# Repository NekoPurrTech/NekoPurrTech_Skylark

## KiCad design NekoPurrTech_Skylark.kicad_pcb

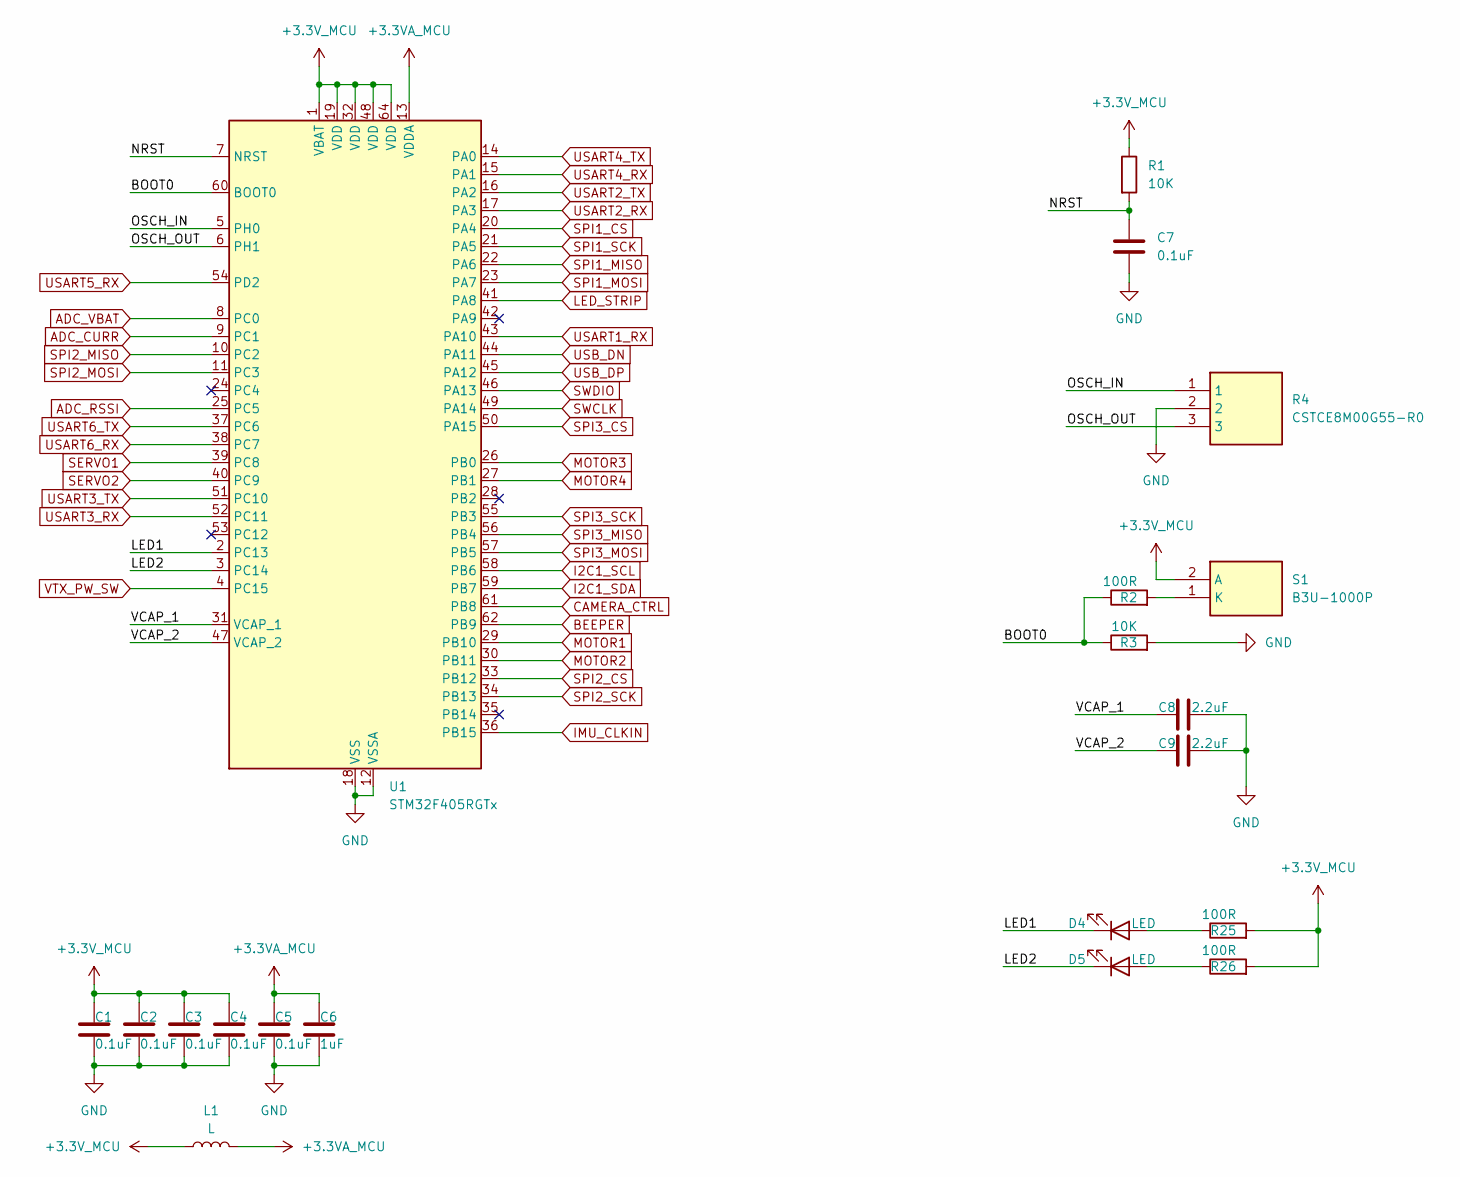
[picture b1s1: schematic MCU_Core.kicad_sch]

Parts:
C1, C2, C3, C4, C5, C7: 0.1uF; C_0402_1005Metric
C6: 1uF; C_0402_1005Metric
C8, C9: 2.2uF; C_0402_1005Metric
D4, D5: LED; LED_0603_1608Metric
L1: L; L_0603_1608Metric
R1, R3: 10K; R_0402_1005Metric
R2, R25, R26: 100R; R_0402_1005Metric
R4: CSTCE8M00G55-R0; CSTCE12M0G55-R0; Manufacturer_Part_Number CSTCE8M00G55-R0; Mouser Part Number 81-CSTCE8M00G55-R0
S1: B3U-1000P; Manufacturer_Part_Number B3U-1000P; Mouser Part Number 653-B3U-1000P
U1: STM32F405RGTx; LQFP-64_10x10mm_P0.5mm

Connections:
+3.3VA_MCU: C5.1, C6.1, L1.2, U1.13 (VDDA)
+3.3V_MCU: C1.1, C2.1, C3.1, C4.1, L1.1, R1.1, R25.2, R26.2, S1.2 (A), U1.1 (VBAT), U1.19 (VDD), U1.32 (VDD), U1.48 (VDD), U1.64 (VDD); also elsewhere on the board
/MCU_Core/BOOT0: R2.1, R3.1, U1.60 (BOOT0)
/MCU_Core/LED1: D4.1 (K), U1.2 (PC13)
/MCU_Core/LED2: D5.1 (K), U1.3 (PC14)
/MCU_Core/NRST: C7.1, R1.2, U1.7 (NRST)
/MCU_Core/OSCH_IN: R4.1, U1.5 (PH0)
/MCU_Core/OSCH_OUT: R4.3, U1.6 (PH1)
/MCU_Core/VCAP_1: C8.1, U1.31 (VCAP_1)
/MCU_Core/VCAP_2: C9.1, U1.47 (VCAP_2)
ADC_CURR: U1.9 (PC1); also elsewhere on the board
ADC_RSSI: U1.25 (PC5); also elsewhere on the board
ADC_VBAT: U1.8 (PC0); also elsewhere on the board
BEEPER: U1.62 (PB9); also elsewhere on the board
CAMERA_CTRL: U1.61 (PB8); also elsewhere on the board
GND: C1.2, C2.2, C3.2, C4.2, C5.2, C6.2, C7.2, C8.2, C9.2, R3.2, R4.2, U1.12 (VSSA), U1.18 (VSS), U1.63 (VSS); also elsewhere on the board
I2C1_SCL: U1.58 (PB6); also elsewhere on the board
I2C1_SDA: U1.59 (PB7); also elsewhere on the board
IMU_CLKIN: U1.36 (PB15); also elsewhere on the board
LED_STRIP: U1.41 (PA8); also elsewhere on the board
MOTOR1: U1.29 (PB10); also elsewhere on the board
MOTOR2: U1.30 (PB11); also elsewhere on the board
MOTOR3: U1.26 (PB0); also elsewhere on the board
MOTOR4: U1.27 (PB1); also elsewhere on the board
unnamed: D4.2 (A), R25.1
unnamed: D5.2 (A), R26.1
unnamed: R2.2, S1.1 (K)
SERVO1: U1.39 (PC8); also elsewhere on the board
SERVO2: U1.40 (PC9); also elsewhere on the board
SPI1_CS: U1.20 (PA4); also elsewhere on the board
SPI1_MISO: U1.22 (PA6); also elsewhere on the board
SPI1_MOSI: U1.23 (PA7); also elsewhere on the board
SPI1_SCK: U1.21 (PA5); also elsewhere on the board
SPI2_CS: U1.33 (PB12); also elsewhere on the board
SPI2_MISO: U1.10 (PC2); also elsewhere on the board
SPI2_MOSI: U1.11 (PC3); also elsewhere on the board
SPI2_SCK: U1.34 (PB13); also elsewhere on the board
SPI3_CS: U1.50 (PA15); also elsewhere on the board
SPI3_MISO: U1.56 (PB4); also elsewhere on the board
SPI3_MOSI: U1.57 (PB5); also elsewhere on the board
SPI3_SCK: U1.55 (PB3); also elsewhere on the board
SWCLK: U1.49 (PA14)
SWDIO: U1.46 (PA13)
USART1_RX: U1.43 (PA10); also elsewhere on the board
USART2_RX: U1.17 (PA3); also elsewhere on the board
USART2_TX: U1.16 (PA2); also elsewhere on the board
USART3_RX: U1.52 (PC11); also elsewhere on the board
USART3_TX: U1.51 (PC10); also elsewhere on the board
USART4_RX: U1.15 (PA1); also elsewhere on the board
USART4_TX: U1.14 (PA0); also elsewhere on the board
USART5_RX: U1.54 (PD2); also elsewhere on the board
USART6_RX: U1.38 (PC7); also elsewhere on the board
USART6_TX: U1.37 (PC6); also elsewhere on the board
USB_DN: U1.44 (PA11); also elsewhere on the board
USB_DP: U1.45 (PA12); also elsewhere on the board
VTX_PW_SW: U1.4 (PC15)

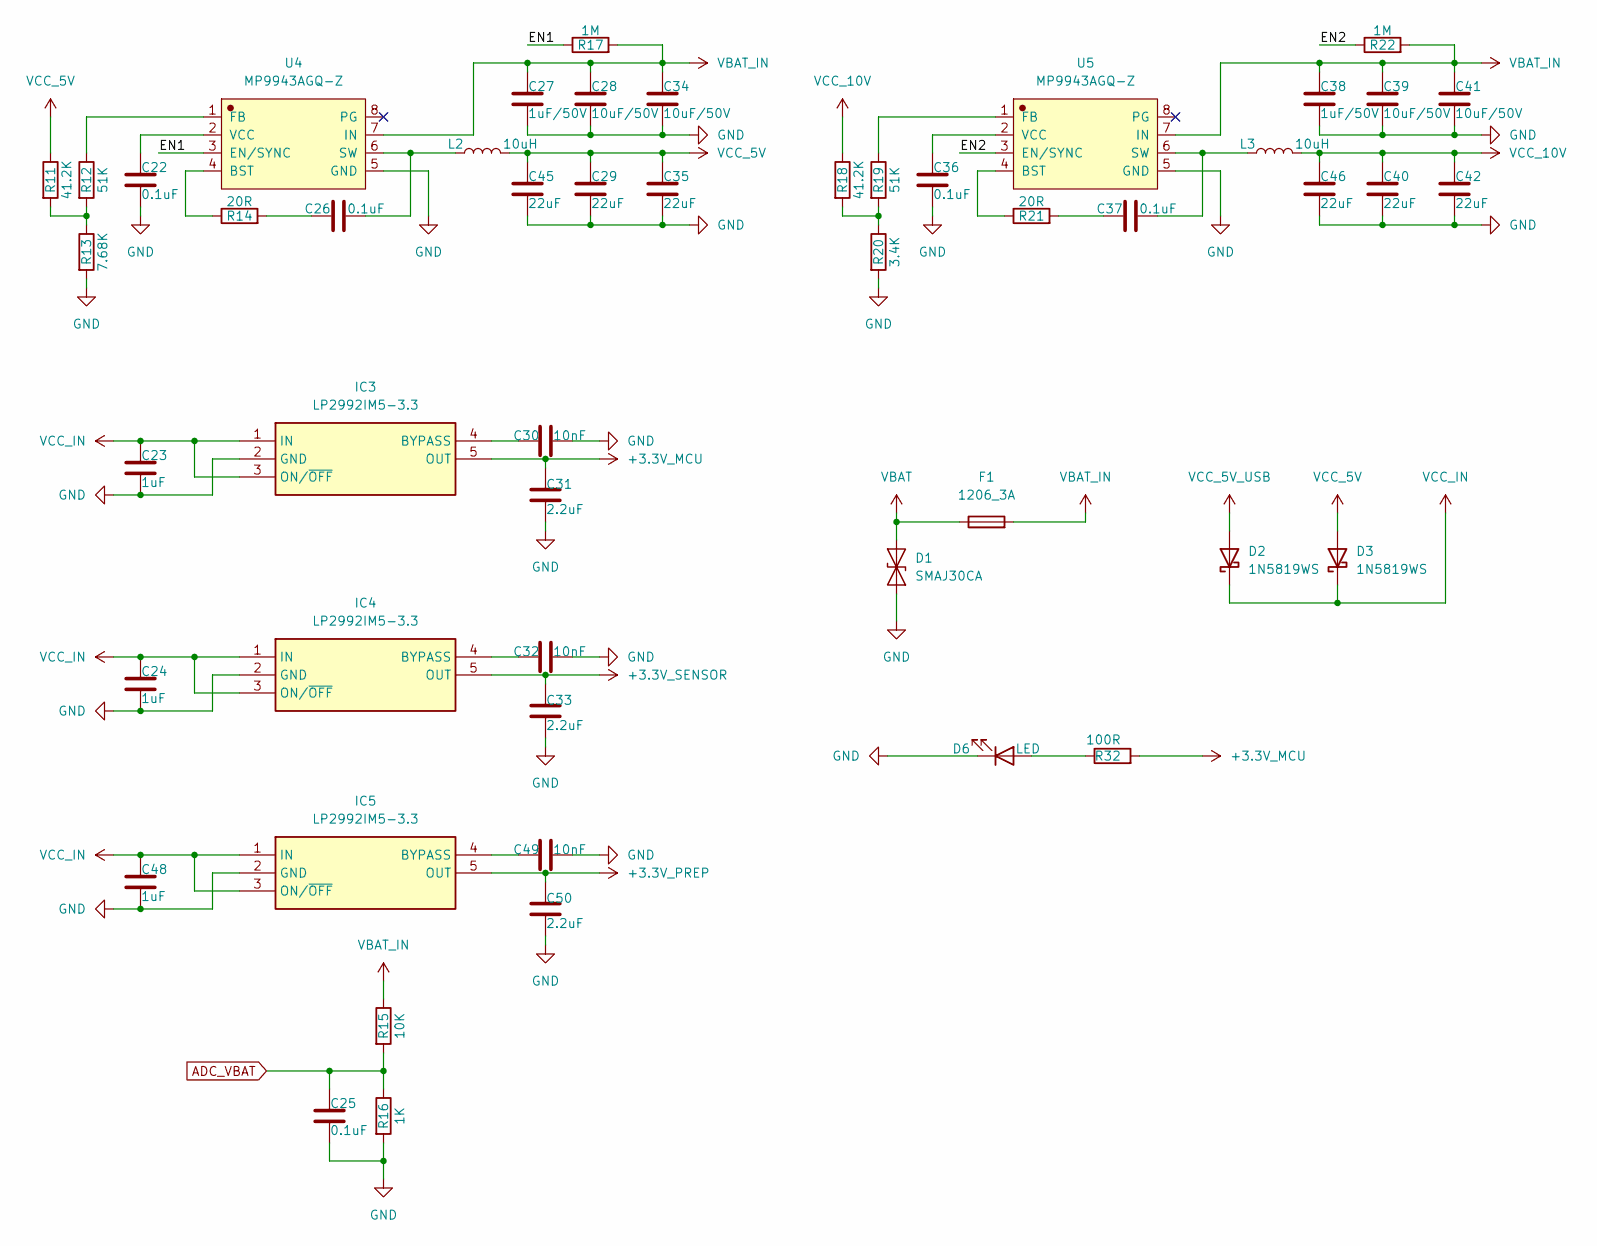
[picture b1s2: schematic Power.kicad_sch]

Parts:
C22, C25, C26, C36, C37: 0.1uF; C_0402_1005Metric
C23, C24, C48: 1uF; C_0603_1608Metric
C27, C38: 1uF/50V; C_0805_2012Metric
C28, C34, C39, C41: 10uF/50V; C_0805_2012Metric
C29, C35, C40, C42, C45, C46: 22uF; C_0805_2012Metric
C30, C32, C49: 10nF; C_0402_1005Metric
C31, C33, C50: 2.2uF; C_0603_1608Metric
D1: SMAJ30CA; D_SMA
D2, D3: 1N5819WS; D_SOD-323
D6: LED; LED_0603_1608Metric
F1: 1206_3A; R_1206_3216Metric
IC3, IC4, IC5: LP2992IM5-3.3; SOT95P280X145-5N; Manufacturer_Part_Number LP2992IM5-3.3; Mouser Part Number 926-LP2992IM5-33
L2, L3: 10uH; L_APV_APH0530
R11, R18: 41.2K; R_0402_1005Metric
R12, R19: 51K; R_0402_1005Metric
R13: 7.68K; R_0402_1005Metric
R14, R21: 20R; R_0402_1005Metric
R15: 10K; R_0402_1005Metric
R16: 1K; R_0402_1005Metric
R17, R22: 1M; R_0402_1005Metric
R20: 3.4K; R_0402_1005Metric
R32: 100R; R_0402_1005Metric
U4, U5: MP9943AGQ-Z; QFN-8_L3.0-W3.0-P0.65

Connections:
+3.3V_MCU: C31.1, IC3.5 (OUT), R32.2; also elsewhere on the board
+3.3V_PREP: C50.1, IC5.5 (OUT); also elsewhere on the board
+3.3V_SENSOR: C33.1, IC4.5 (OUT); also elsewhere on the board
/Power/EN1: R17.1, U4.3 (EN/SYNC)
/Power/EN2: R22.1, U5.3 (EN/SYNC)
ADC_VBAT: C25.1, R15.2, R16.1; also elsewhere on the board
GND: C22.2, C23.2, C24.2, C25.2, C27.2, C28.2, C29.2, C30.2, C31.2, C32.2, C33.2, C34.2, C35.2, C36.2, C38.2, C39.2, C40.2, C41.2, C42.2, C45.2, C46.2, C48.2, C49.2, C50.2, D1.1 (A1), D6.1 (K), IC3.2 (GND), IC4.2 (GND), IC5.2 (GND), R13.2, R16.2, R20.2, U4.5 (GND), U5.5 (GND); also elsewhere on the board
unnamed: C26.1, R14.2
unnamed: C37.1, R21.2
unnamed: D6.2 (A), R32.1
unnamed: C30.1, IC3.4 (BYPASS)
unnamed: C32.1, IC4.4 (BYPASS)
unnamed: C49.1, IC5.4 (BYPASS)
unnamed: R11.2, R12.2, R13.1
unnamed: R18.2, R19.2, R20.1
unnamed: R14.1, U4.4 (BST)
unnamed: R12.1, U4.1 (FB)
unnamed: C26.2, L2.1, U4.6 (SW)
unnamed: C22.1, U4.2 (VCC)
unnamed: R21.1, U5.4 (BST)
unnamed: R19.1, U5.1 (FB)
unnamed: C37.2, L3.1, U5.6 (SW)
unnamed: C36.1, U5.2 (VCC)
VBAT: D1.2 (A2), F1.1; also elsewhere on the board
VBAT_IN: C27.1, C28.1, C34.1, C38.1, C39.1, C41.1, F1.2, R15.1, R17.2, R22.2, U4.7 (IN), U5.7 (IN)
VCC_5V: C29.1, C35.1, C45.1, D3.2 (A), L2.2, R11.1
VCC_5V_USB: D2.2 (A); also elsewhere on the board
VCC_10V: C40.1, C42.1, C46.1, L3.2, R18.1; also elsewhere on the board
VCC_IN: C23.1, C24.1, C48.1, D2.1 (K), D3.1 (K), IC3.1 (IN), IC3.3 (ON/~OFF), IC4.1 (IN), IC4.3 (ON/~OFF), IC5.1 (IN), IC5.3 (ON/~OFF); also elsewhere on the board

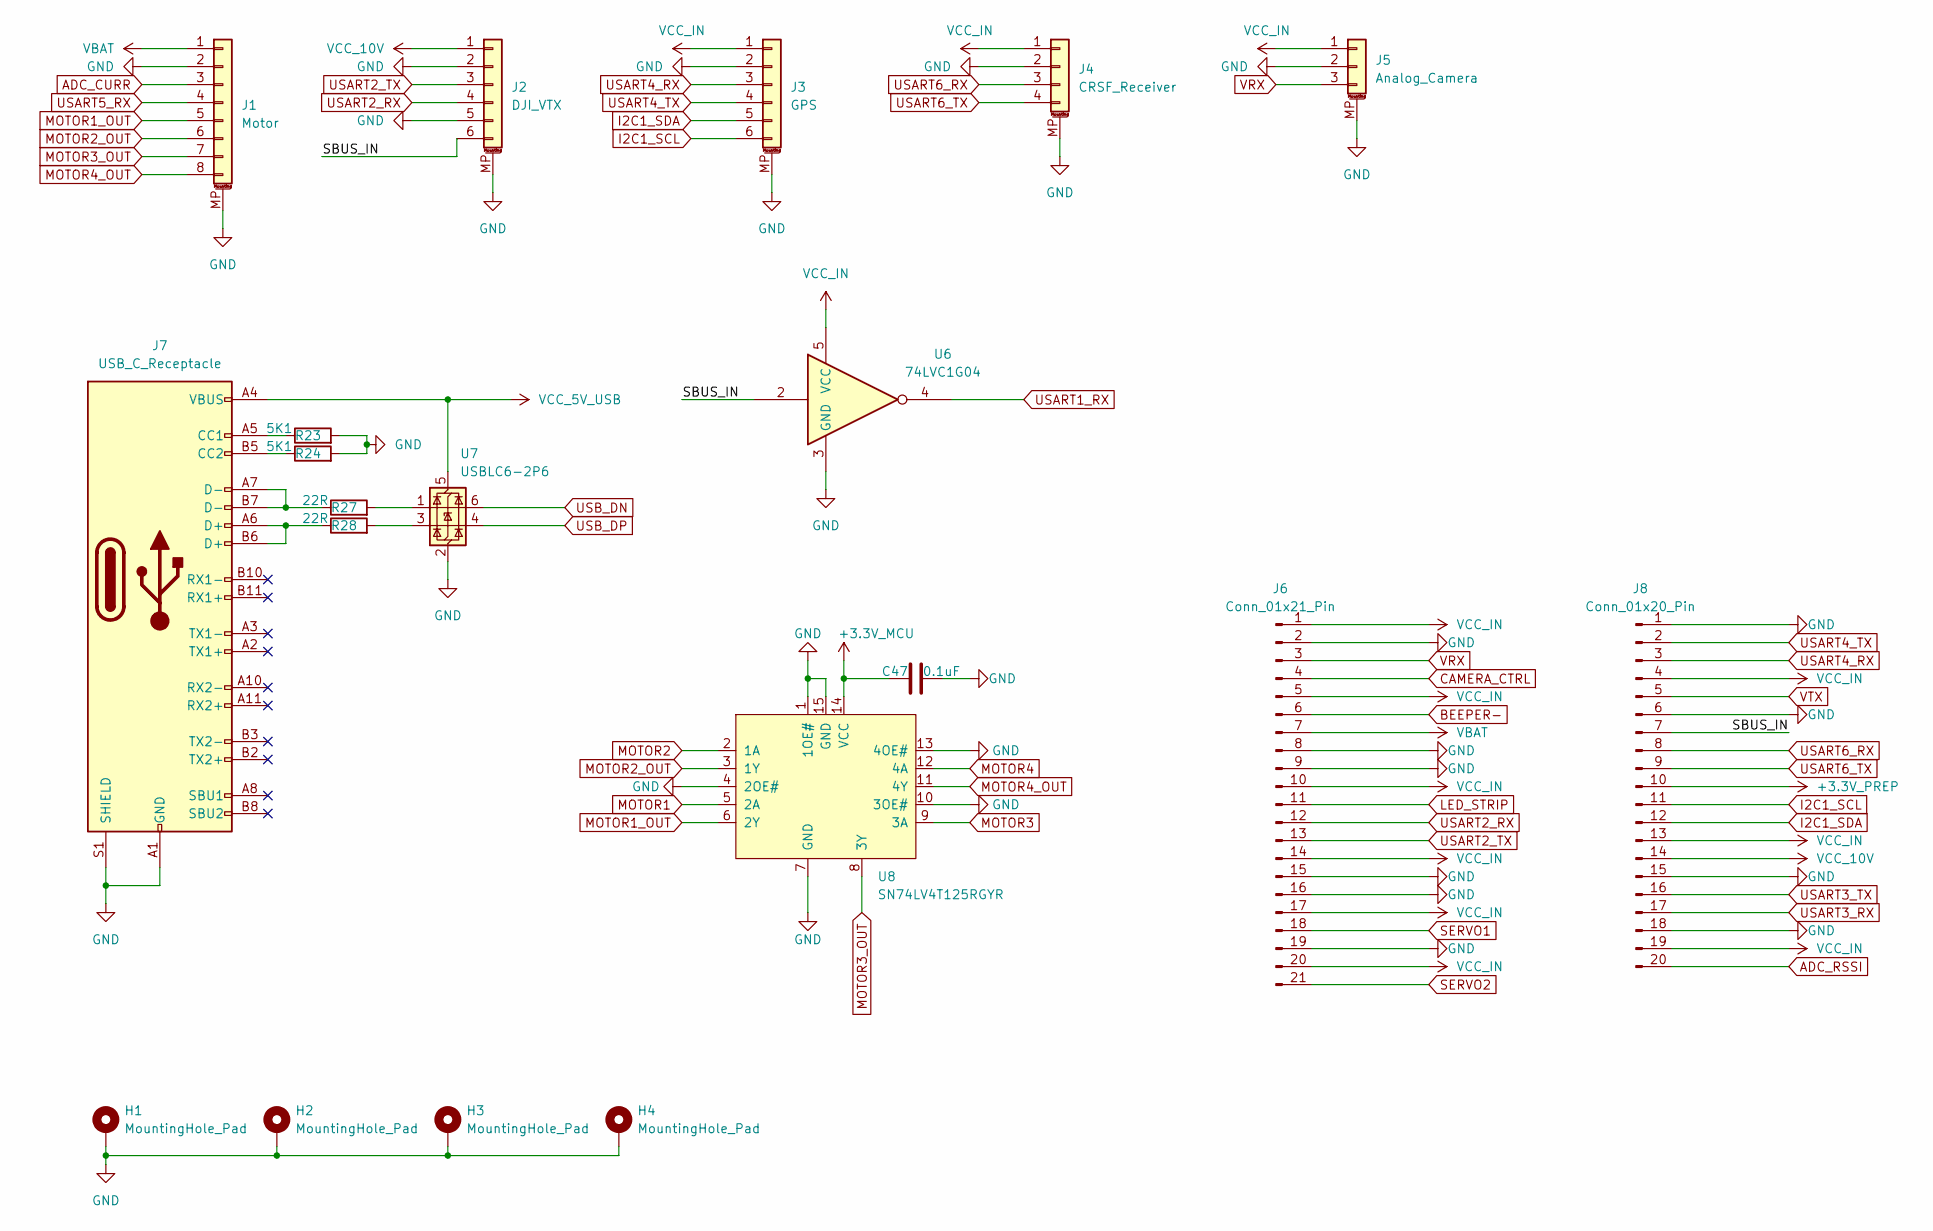
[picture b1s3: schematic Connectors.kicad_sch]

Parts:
C47: 0.1uF; C_0402_1005Metric
H1, H2, H3, H4: MountingHole_Pad; MountingHole_3.2mm_M3_DIN965_Pad
J1: Motor; JST_SH_SM08B-SRSS-TB_1x08-1MP_P1.00mm_Horizontal
J2: DJI_VTX; JST_SH_SM06B-SRSS-TB_1x06-1MP_P1.00mm_Horizontal
J3: GPS; JST_SH_SM06B-SRSS-TB_1x06-1MP_P1.00mm_Horizontal
J4: CRSF_Receiver; JST_SH_SM04B-SRSS-TB_1x04-1MP_P1.00mm_Horizontal
J5: Analog_Camera; JST_SH_SM03B-SRSS-TB_1x03-1MP_P1.00mm_Horizontal
J6: Conn_01x21_Pin; Betaflight_Pad_F
J7: USB_C_Receptacle; USB-C_halfboard
J8: Conn_01x20_Pin; Betaflight_Pad_B
R23, R24: 5K1; R_0402_1005Metric
R27, R28: 22R; R_0402_1005Metric
U6: 74LVC1G04; SOT-23-5
U7: USBLC6-2P6; SOT-666
U8: SN74LV4T125RGYR; VQFN-14_L3.5-W3.5-P0.50-BL-EP

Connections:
+3.3V_MCU: C47.1, U8.14 (VCC); also elsewhere on the board
+3.3V_PREP: J8.10; also elsewhere on the board
/Connectors/SBUS_IN: J2.6, J8.7, U6.2
ADC_CURR: J1.3; also elsewhere on the board
ADC_RSSI: J8.20; also elsewhere on the board
BEEPER-: J6.6; also elsewhere on the board
CAMERA_CTRL: J6.4; also elsewhere on the board
GND: C47.2, H1.1, H2.1, H3.1, H4.1, J1.2, J1.MP (MountPin), J2.2, J2.5, J2.MP (MountPin), J3.2, J3.MP (MountPin), J4.2, J4.MP (MountPin), J5.2, J5.MP (MountPin), J6.2, J6.8, J6.9, J6.15, J6.16, J6.19, J7.A1 (GND), J7.A12 (GND), J7.B1 (GND), J7.B12 (GND), J7.S1 (SHIELD), J8.1, J8.6, J8.15, J8.18, R23.2, R24.2, U6.3 (GND), U7.2 (GND), U8.1 (1OE#), U8.4 (2OE#), U8.7 (GND), U8.10 (3OE#), U8.13 (4OE#), U8.15 (GND); also elsewhere on the board
I2C1_SCL: J3.6, J8.11; also elsewhere on the board
I2C1_SDA: J3.5, J8.12; also elsewhere on the board
LED_STRIP: J6.11; also elsewhere on the board
MOTOR1: U8.5 (2A); also elsewhere on the board
MOTOR1_OUT: J1.5, U8.6 (2Y)
MOTOR2: U8.2 (1A); also elsewhere on the board
MOTOR2_OUT: J1.6, U8.3 (1Y)
MOTOR3: U8.9 (3A); also elsewhere on the board
MOTOR3_OUT: J1.7, U8.8 (3Y)
MOTOR4: U8.12 (4A); also elsewhere on the board
MOTOR4_OUT: J1.8, U8.11 (4Y)
unnamed: J7.A5 (CC1), R23.1
unnamed: J7.B5 (CC2), R24.1
unnamed: J7.A6 (D+), J7.B6 (D+), R28.1
unnamed: J7.A7 (D-), J7.B7 (D-), R27.1
unnamed: R27.2, U7.1 (I/O1)
unnamed: R28.2, U7.3 (I/O2)
SERVO1: J6.18; also elsewhere on the board
SERVO2: J6.21; also elsewhere on the board
USART1_RX: U6.4; also elsewhere on the board
USART2_RX: J2.4, J6.12; also elsewhere on the board
USART2_TX: J2.3, J6.13; also elsewhere on the board
USART3_RX: J8.17; also elsewhere on the board
USART3_TX: J8.16; also elsewhere on the board
USART4_RX: J3.3, J8.3; also elsewhere on the board
USART4_TX: J3.4, J8.2; also elsewhere on the board
USART5_RX: J1.4; also elsewhere on the board
USART6_RX: J4.3, J8.8; also elsewhere on the board
USART6_TX: J4.4, J8.9; also elsewhere on the board
USB_DN: U7.6 (I/O1); also elsewhere on the board
USB_DP: U7.4 (I/O2); also elsewhere on the board
VBAT: J1.1, J6.7; also elsewhere on the board
VCC_5V_USB: J7.A4 (VBUS), J7.A9 (VBUS), J7.B4 (VBUS), J7.B9 (VBUS), U7.5 (VBUS); also elsewhere on the board
VCC_10V: J2.1, J8.14; also elsewhere on the board
VCC_IN: J3.1, J4.1, J5.1, J6.1, J6.5, J6.10, J6.14, J6.17, J6.20, J8.4, J8.13, J8.19, U6.5 (VCC); also elsewhere on the board
VRX: J5.3, J6.3; also elsewhere on the board
VTX: J8.5; also elsewhere on the board

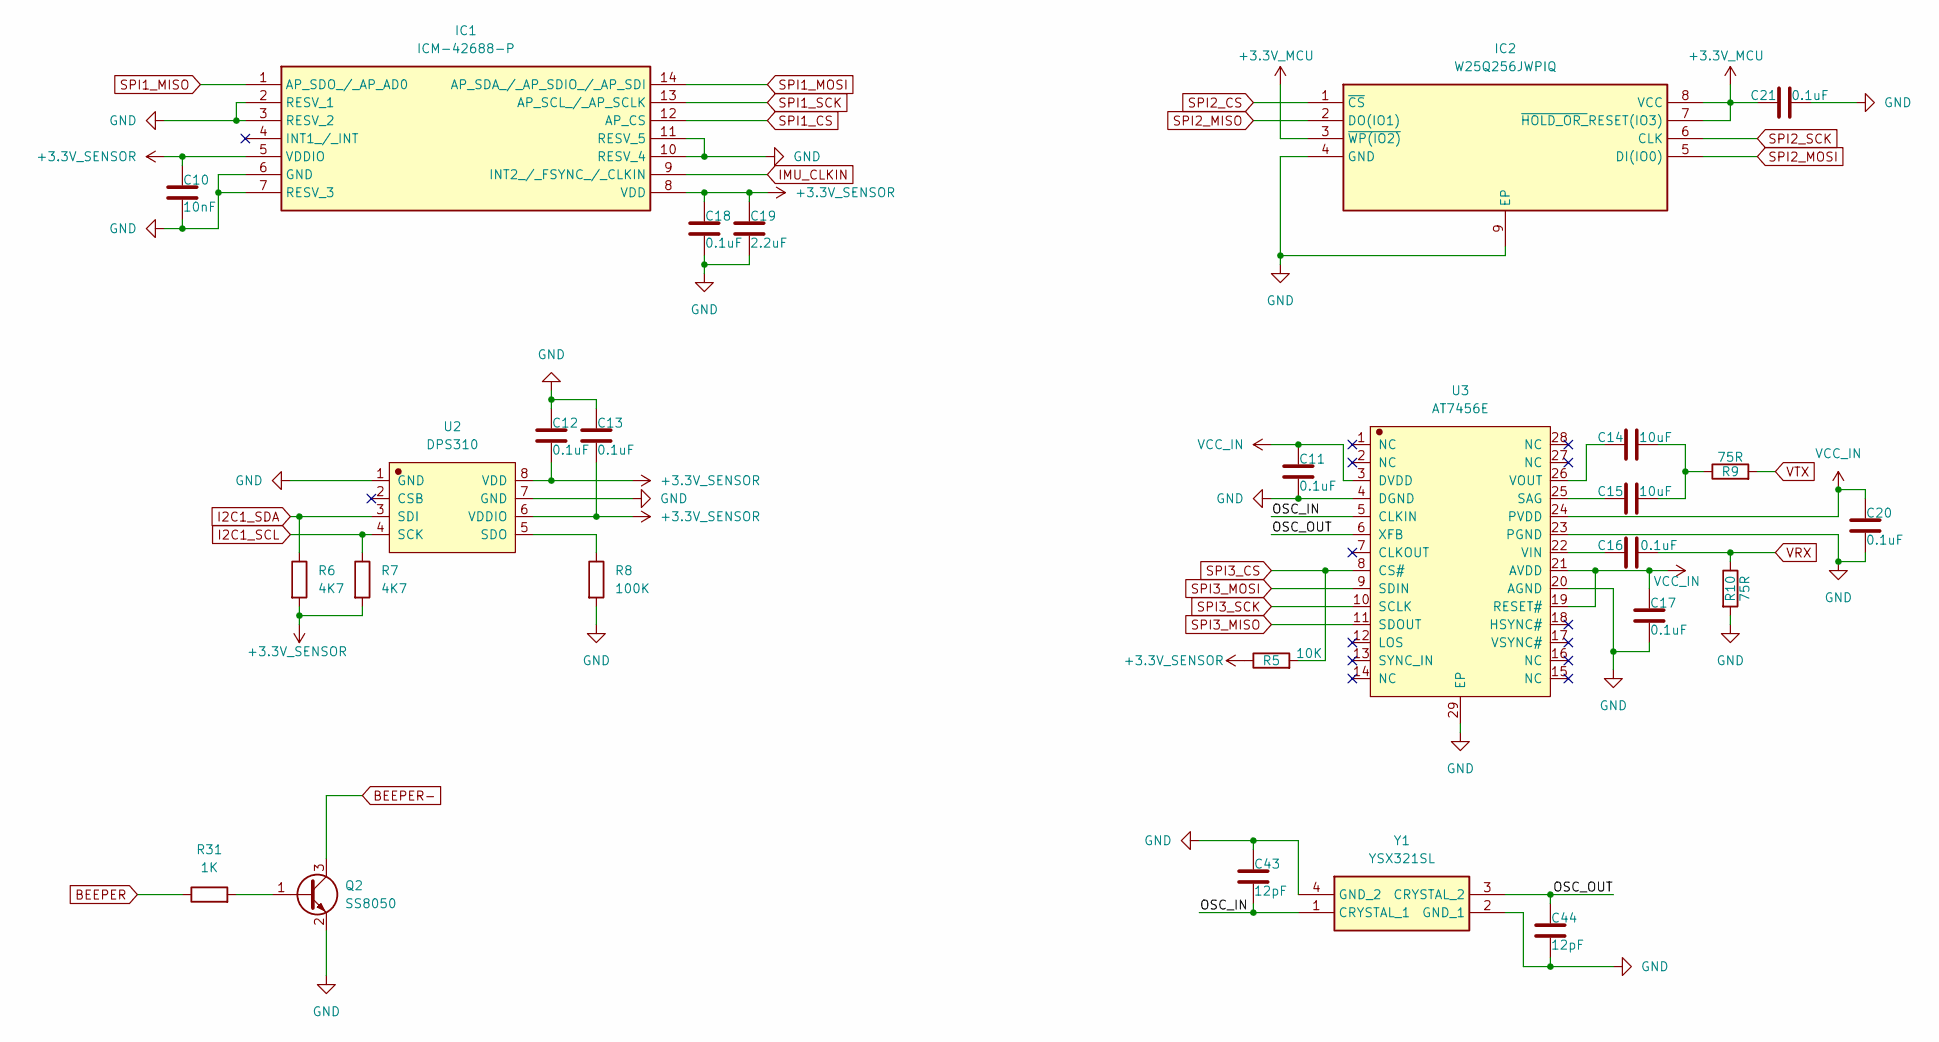
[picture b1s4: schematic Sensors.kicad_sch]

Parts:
C10: 10nF; C_0402_1005Metric
C11, C12, C13, C16, C17, C18, C20, C21: 0.1uF; C_0402_1005Metric
C14, C15: 10uF; C_0402_1005Metric
C19: 2.2uF; C_0402_1005Metric
C43, C44: 12pF; C_0402_1005Metric
IC1: ICM-42688-P; IIM42352; Manufacturer_Part_Number ICM-42688-P; Mouser Part Number 410-ICM-42688-P
IC2: W25Q256JWPIQ; SON127P600X500X80-9N-D; Manufacturer_Part_Number W25Q256JWPIQ; Mouser Part Number 454-W25Q256JWPIQ
Q2: SS8050; SOT-23
R5: 10K; R_0402_1005Metric
R6, R7: 4K7; R_0402_1005Metric
R8: 100K; R_0402_1005Metric
R9, R10: 75R; R_0402_1005Metric
R31: 1K; R_0402_1005Metric
U2: DPS310; WLGA-8_L2.5-W2.0-P0.65-TR_DPS422
U3: AT7456E; TSSOP-28_L9.7-W4.4-P0.65-LS6.4-BL-EP-2
Y1: YSX321SL; Manufacturer_Part_Number YSX321SL

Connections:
+3.3V_MCU: C21.1, IC2.3 (~WP(IO2)), IC2.7 (~HOLD_OR_RESET(IO3)), IC2.8 (VCC); also elsewhere on the board
+3.3V_SENSOR: C10.1, C12.2, C13.2, C18.1, C19.1, IC1.5 (VDDIO), IC1.8 (VDD), R5.1, R6.2, R7.2, U2.6 (VDDIO), U2.8 (VDD); also elsewhere on the board
/Sensors/OSC_IN: C43.2, U3.5 (CLKIN), Y1.1 (CRYSTAL_1)
/Sensors/OSC_OUT: C44.1, U3.6 (XFB), Y1.3 (CRYSTAL_2)
BEEPER: R31.1; also elsewhere on the board
BEEPER-: Q2.3 (C); also elsewhere on the board
GND: C10.2, C11.2, C12.1, C13.1, C17.2, C18.2, C19.2, C20.2, C21.2, C43.1, C44.2, IC1.2 (RESV_1), IC1.3 (RESV_2), IC1.6 (GND), IC1.7 (RESV_3), IC1.10 (RESV_4), IC1.11 (RESV_5), IC2.4 (GND), IC2.9 (EP), Q2.2 (E), R8.2, R10.2, U2.1 (GND), U2.7 (GND), U3.4 (DGND), U3.20 (AGND), U3.23 (PGND), U3.29 (EP), Y1.2 (GND_1), Y1.4 (GND_2); also elsewhere on the board
I2C1_SCL: R7.1, U2.4 (SCK); also elsewhere on the board
I2C1_SDA: R6.1, U2.3 (SDI); also elsewhere on the board
IMU_CLKIN: IC1.9 (INT2_/_FSYNC_/_CLKIN); also elsewhere on the board
unnamed: C14.2, C15.2, R9.1
unnamed: Q2.1 (B), R31.2
unnamed: R8.1, U2.5 (SDO)
unnamed: C15.1, U3.25 (SAG)
unnamed: C16.1, U3.22 (VIN)
unnamed: C14.1, U3.26 (VOUT)
SPI1_CS: IC1.12 (AP_CS); also elsewhere on the board
SPI1_MISO: IC1.1 (AP_SDO_/_AP_AD0); also elsewhere on the board
SPI1_MOSI: IC1.14 (AP_SDA_/_AP_SDIO_/_AP_SDI); also elsewhere on the board
SPI1_SCK: IC1.13 (AP_SCL_/_AP_SCLK); also elsewhere on the board
SPI2_CS: IC2.1 (~CS); also elsewhere on the board
SPI2_MISO: IC2.2 (DO(IO1)); also elsewhere on the board
SPI2_MOSI: IC2.5 (DI(IO0)); also elsewhere on the board
SPI2_SCK: IC2.6 (CLK); also elsewhere on the board
SPI3_CS: R5.2, U3.8 (CS#); also elsewhere on the board
SPI3_MISO: U3.11 (SDOUT); also elsewhere on the board
SPI3_MOSI: U3.9 (SDIN); also elsewhere on the board
SPI3_SCK: U3.10 (SCLK); also elsewhere on the board
VCC_IN: C11.1, C17.1, C20.1, U3.3 (DVDD), U3.19 (RESET#), U3.21 (AVDD), U3.24 (PVDD); also elsewhere on the board
VRX: C16.2, R10.1; also elsewhere on the board
VTX: R9.2; also elsewhere on the board

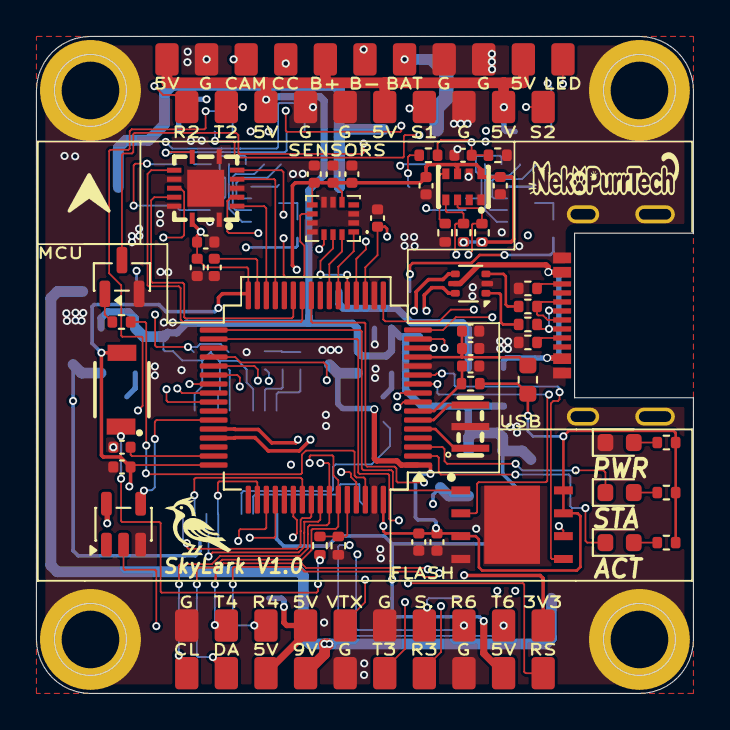
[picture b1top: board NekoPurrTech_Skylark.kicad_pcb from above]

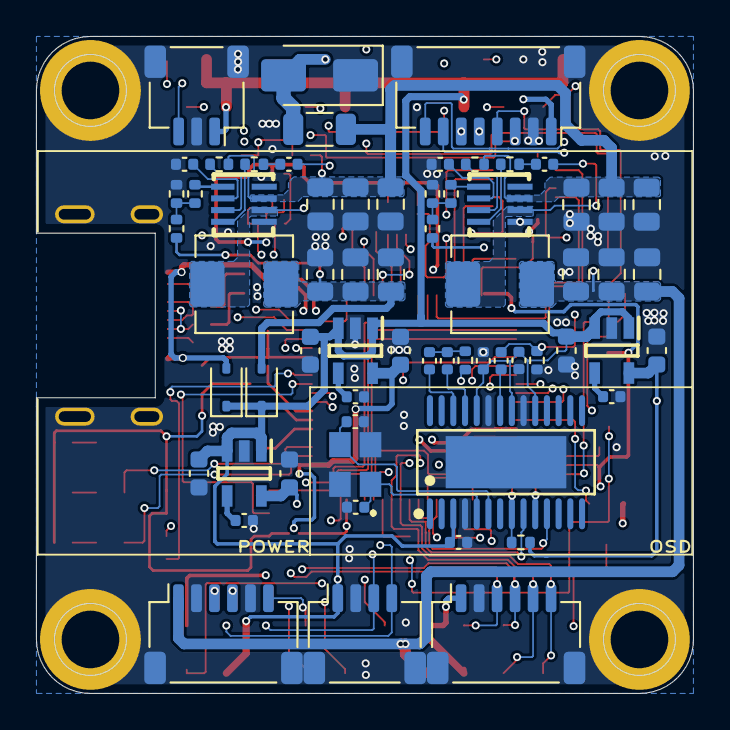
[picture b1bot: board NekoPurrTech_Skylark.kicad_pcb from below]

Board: 4 copper layers, 36.5 x 36.5 mm, 118 parts (64 on the bottom side), 101 nets.

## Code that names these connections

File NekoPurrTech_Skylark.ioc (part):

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Mcu.Name=STM32F405RGTx
Mcu.Package=LQFP64
Mcu.UserName=STM32F405RGTx
PA0-WKUP.Mode=Asynchronous
PA0-WKUP.Signal=UART4_TX
PA1.Mode=Asynchronous
PA1.Signal=UART4_RX
PA10.Mode=Asynchronous
PA10.Signal=USART1_RX
PA11.Mode=Device_Only
PA11.Signal=USB_OTG_FS_DM
PA12.Mode=Device_Only
PA12.Signal=USB_OTG_FS_DP
PA13.Mode=Serial_Wire
PA13.Signal=SYS_JTMS-SWDIO
PA14.Mode=Serial_Wire
PA14.Signal=SYS_JTCK-SWCLK
PA15.GPIOParameters=GPIO_Label
PA15.GPIO_Label=SPI3_CS
PA15.Signal=GPIO_Output
PA2.Mode=Asynchronous
PA2.Signal=USART2_TX
PA3.Mode=Asynchronous
PA3.Signal=USART2_RX
PA4.GPIOParameters=GPIO_Label
PA4.GPIO_Label=SPI1_CS
PA4.Signal=GPIO_Output
PA5.Mode=Full_Duplex_Master
PA5.Signal=SPI1_SCK
PA6.Mode=Full_Duplex_Master
PA6.Signal=SPI1_MISO
PA7.Mode=Full_Duplex_Master
PA7.Signal=SPI1_MOSI
PA8.Mode=I2C
PA8.Signal=I2C3_SCL
PA9.Mode=Asynchronous
PA9.Signal=USART1_TX
PB0.Signal=S_TIM3_CH3
PB1.Signal=S_TIM3_CH4
PB10.Signal=S_TIM2_CH3
PB11.Signal=S_TIM2_CH4
PB12.GPIOParameters=GPIO_Label
PB12.GPIO_Label=SPI2_CS
PB12.Signal=GPIO_Output
PB13.Mode=Full_Duplex_Master
PB13.Signal=SPI2_SCK
PB15.GPIOParameters=GPIO_Label
PB15.GPIO_Label=GYRO_CLK
PB15.Signal=GPIO_Output
PB3.Mode=Full_Duplex_Master
PB3.Signal=SPI3_SCK
PB4.Mode=Full_Duplex_Master
PB4.Signal=SPI3_MISO
PB5.Mode=Full_Duplex_Master
PB5.Signal=SPI3_MOSI
PB6.Mode=I2C
PB6.Signal=I2C1_SCL
PB7.Mode=I2C
PB7.Signal=I2C1_SDA
PB8.GPIOParameters=GPIO_Label
PB8.GPIO_Label=CAMERA_CTRL
PB8.Signal=GPIO_Output
PB9.GPIOParameters=GPIO_Label
PB9.GPIO_Label=BEEPER
PB9.Signal=GPIO_Output
PC0.Signal=ADCx_IN10
PC1.Signal=ADCx_IN11
PC10.Mode=Asynchronous
PC10.Signal=USART3_TX
PC11.Mode=Asynchronous
PC11.Signal=USART3_RX
PC12.Mode=Asynchronous
PC12.Signal=UART5_TX
PC13-ANTI_TAMP.GPIOParameters=GPIO_Label
PC13-ANTI_TAMP.GPIO_Label=LED_1
PC13-ANTI_TAMP.Signal=GPIO_Output
PC14-OSC32_IN.GPIOParameters=GPIO_Label
PC14-OSC32_IN.GPIO_Label=LED_2
PC14-OSC32_IN.Signal=GPIO_Output
PC2.Mode=Full_Duplex_Master
PC2.Signal=SPI2_MISO
PC3.Mode=Full_Duplex_Master
PC3.Signal=SPI2_MOSI
PC5.Signal=ADCx_IN15
PC6.Mode=Asynchronous
PC6.Signal=USART6_TX
PC7.Mode=Asynchronous
PC7.Signal=USART6_RX
PC8.Signal=S_TIM8_CH3
PC9.Mode=I2C
PC9.Signal=I2C3_SDA
PD2.Mode=Asynchronous
PD2.Signal=UART5_RX
PH0-OSC_IN.Mode=HSE-External-Oscillator
PH0-OSC_IN.Signal=RCC_OSC_IN
PH1-OSC_OUT.Mode=HSE-External-Oscillator
PH1-OSC_OUT.Signal=RCC_OSC_OUT
RCC.HSE_VALUE=25000000
RCC.SYSCLKFreq_VALUE=16000000
board=custom

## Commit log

2026-01-19 Update SCH
2026-01-21 Finished SCH
2026-01-22 Updated PCB Layout
2026-01-22 Update PCB Layout
2026-01-24 Finished PCB V1.0
2026-01-25 Finished PCB SilkScreen V1.0
